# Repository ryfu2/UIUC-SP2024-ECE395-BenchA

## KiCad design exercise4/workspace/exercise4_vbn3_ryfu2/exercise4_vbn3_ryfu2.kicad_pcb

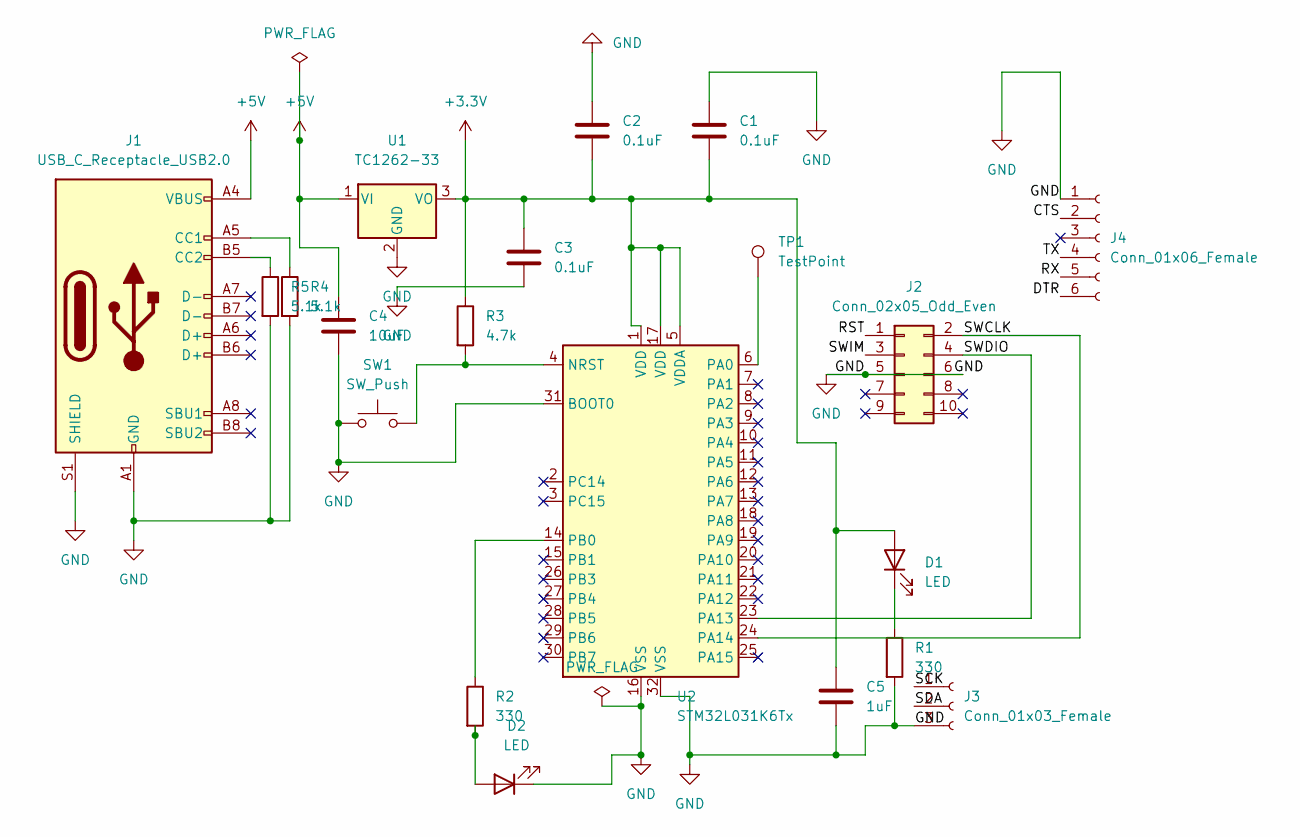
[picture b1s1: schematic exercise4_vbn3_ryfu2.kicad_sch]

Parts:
C1, C2, C3: 0.1uF; C_0805_2012Metric_Pad1.18x1.45mm_HandSolder
C4: 10uF; C_0805_2012Metric_Pad1.18x1.45mm_HandSolder
C5: 1uF; C_0805_2012Metric_Pad1.18x1.45mm_HandSolder
D1, D2: LED; LED_0805_2012Metric_Pad1.15x1.40mm_HandSolder
J1: USB_C_Receptacle_USB2.0; USB_C_Receptacle_GCT_USB4085
J2: Conn_02x05_Odd_Even; PinHeader_2x05_P2.54mm_Vertical
J3: Conn_01x03_Female; PinHeader_1x03_P2.54mm_Vertical
J4: Conn_01x06_Female; PinHeader_1x06_P2.54mm_Vertical
R1, R2: 330; R_0805_2012Metric_Pad1.20x1.40mm_HandSolder
R3: 4.7k; R_0805_2012Metric_Pad1.20x1.40mm_HandSolder
R4, R5: 5.1k; R_0805_2012Metric_Pad1.20x1.40mm_HandSolder
SW1: SW_Push; SW_PUSH_6mm_H4.3mm
TP1: TestPoint; TestPoint_Keystone_5010-5014_Multipurpose
U1: TC1262-33; SOT-223-3_TabPin2
U2: STM32L031K6Tx; LQFP-32_7x7mm_P0.8mm

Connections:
+3V3: C1.2, C2.2, C3.1, C5.1, D1.2 (A), R3.1, U1.3 (VO), U2.1 (VDD), U2.5 (VDDA), U2.17 (VDD)
+5V: C4.1, J1.A4 (VBUS), J1.A9 (VBUS), J1.B4 (VBUS), J1.B9 (VBUS), U1.1 (VI)
/CTS: J4.2
/DTR: J4.6
/RST: J2.1
/RX: J4.5
/SCK: J3.1
/SDA: J3.2
/SWCLK: J2.2, U2.24 (PA14)
/SWDIO: J2.4, U2.23 (PA13)
/SWIM: J2.3
/TX: J4.4
GND: C1.1, C2.1, C3.2, C4.2, C5.2, D2.1 (K), J1.A1 (GND), J1.A12 (GND), J1.B1 (GND), J1.B12 (GND), J1.S1 (SHIELD), J2.5, J2.6, J3.3, J4.1, R1.2, R4.2, R5.2, SW1.1, U1.2 (GND), U2.16 (VSS), U2.31 (BOOT0), U2.32 (VSS)
unnamed: D1.1 (K), R1.1
unnamed: J1.A5 (CC1), R4.1
unnamed: J1.B5 (CC2), R5.1
unnamed: R2.1, U2.14 (PB0)
unnamed: D2.2 (A), R2.2
unnamed: R3.2, SW1.2, U2.4 (NRST)
unnamed: TP1.1, U2.6 (PA0)

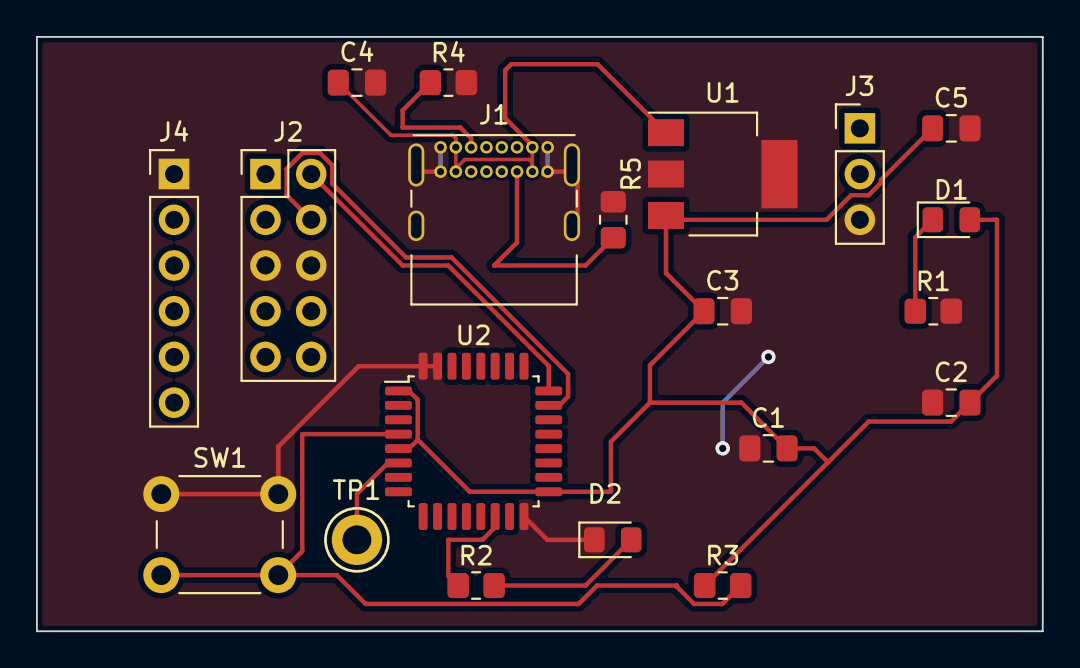
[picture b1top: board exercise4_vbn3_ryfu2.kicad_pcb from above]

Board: 2 copper layers, 55.9 x 33.0 mm, 20 parts (0 on the bottom side), 12 nets.
